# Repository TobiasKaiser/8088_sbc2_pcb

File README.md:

8088_scb2
========

See [my website][1] for more information on this PCB.

Firmware
--------

The corresponding firmware can be found in the [8088_sbc2_firmware][2] repository.

License
-------

* FT232RL component comes from a [component collection][3] from Werner Almesberger: 

Everything else:

Copyright (c) 2016 Tobias Kaiser <mail@tb-kaiser.de>

Permission is hereby granted, free of charge, to any person obtaining a copy of this hardware, software, and associated documentation files (the "Product"), to deal in the Product without restriction, including without limitation the rights to use, copy, modify, merge, publish, distribute, sublicense, and/or sell copies of the Product, and to permit persons to whom the Product is furnished to do so, subject to the following conditions:

The above copyright notice and this permission notice shall be included in all copies or substantial portions of the Product.

THE PRODUCT IS PROVIDED "AS IS", WITHOUT WARRANTY OF ANY KIND, EXPRESS OR IMPLIED, INCLUDING BUT NOT LIMITED TO THE WARRANTIES OF MERCHANTABILITY, FITNESS FOR A PARTICULAR PURPOSE AND NONINFRINGEMENT. IN NO EVENT SHALL THE AUTHORS OR COPYRIGHT HOLDERS BE LIABLE FOR ANY CLAIM, DAMAGES OR OTHER LIABILITY, WHETHER IN AN ACTION OF CONTRACT, TORT OR OTHERWISE, ARISING FROM, OUT OF OR IN CONNECTION WITH THE PRODUCT OR THE USE OR OTHER DEALINGS IN THE PRODUCT.

[1]: http://www.tb-kaiser.de/pcbs/8088_sbc2_2016_12_22/
[2]: https://github.com/TobiasKaiser/8088_sbc2_firmware/
[3]: http://projects.qi-hardware.com/index.php/p/kicad-libs/source/tree/master/components/ft232rl.lib

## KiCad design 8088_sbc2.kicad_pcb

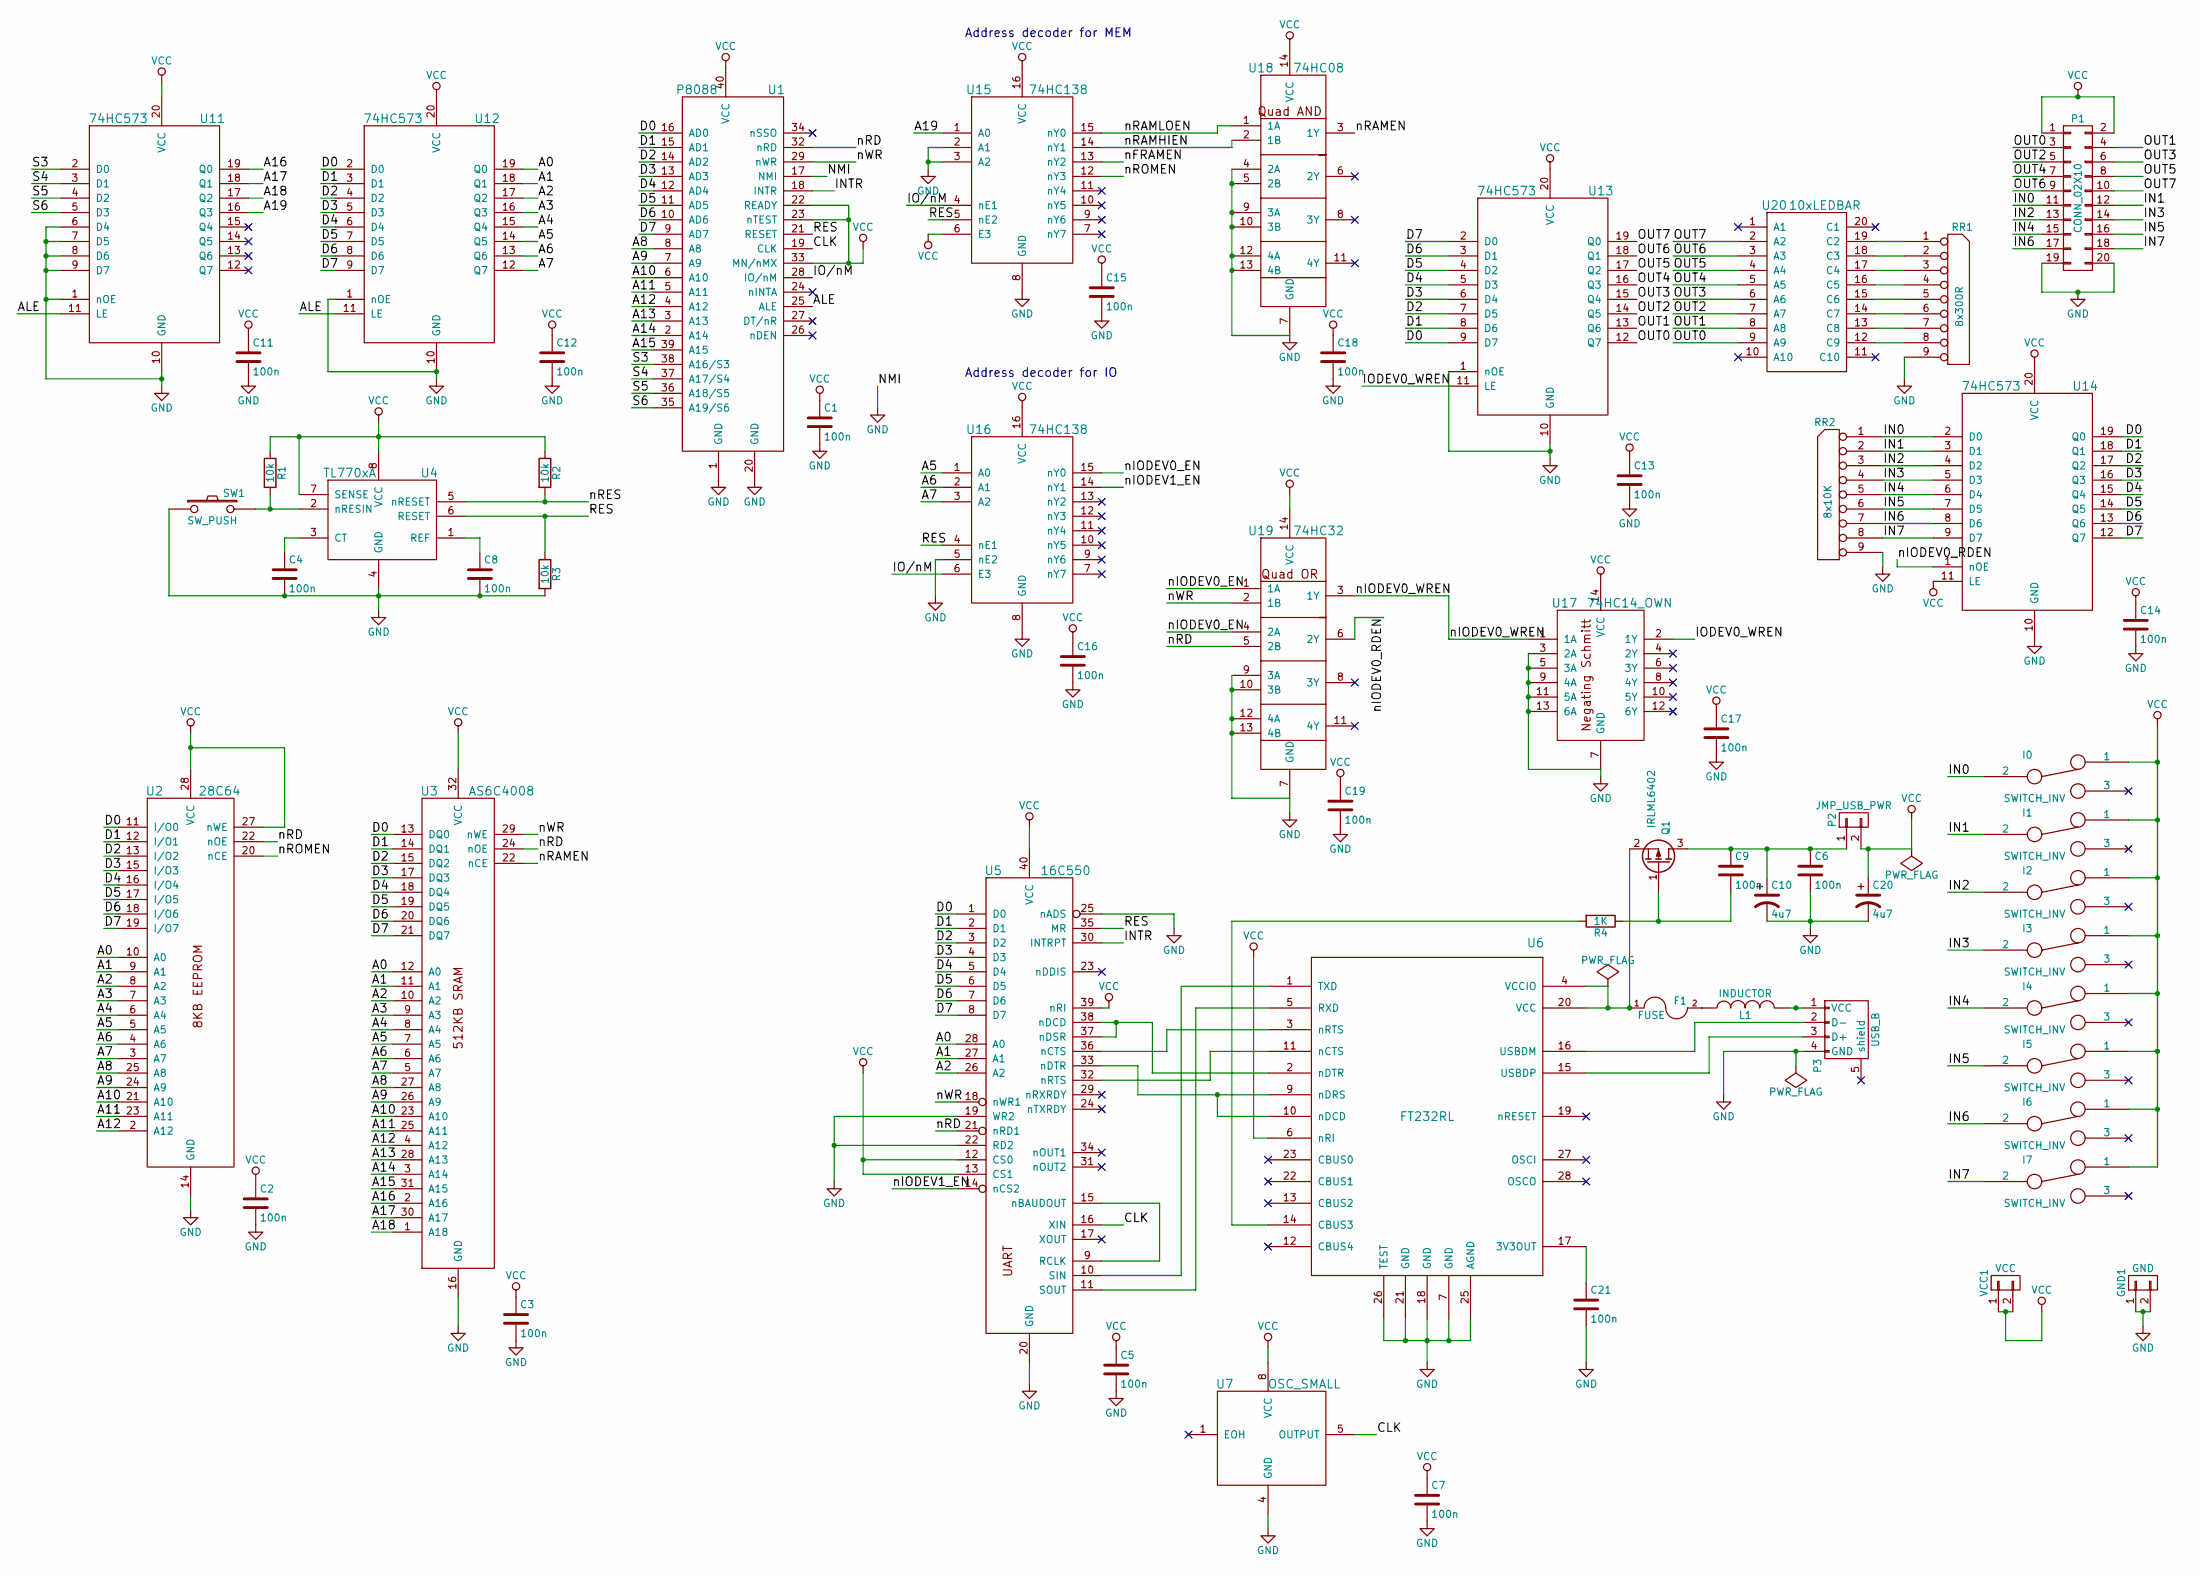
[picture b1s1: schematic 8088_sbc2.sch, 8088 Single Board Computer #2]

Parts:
C1, C2, C3, C4, C5, C6, C7, C8, C9, C11, C12, C13, C14, C15, C16, C17, C18, C19, C21: 100n; C_Disc_D3_P2.5
C10: 4u7; C_Radial_D6.3_L11.2_P2.5
C20: 4u7; C_Radial_D7.5_L11.2_P2.5
F1: FUSE; C_1206_HandSoldering
GND1: GND; Pin_Header_Straight_1x02
I0, I1, I2, I3, I4, I5, I6, I7: SWITCH_INV; EG1218
L1: INDUCTOR; C_0805_HandSoldering
P1: CONN_02X10; Pin_Header_Straight_2x10
P2: JMP_USB_PWR; Pin_Header_Straight_1x02
P3: USB_B
Q1: IRLML6402; SOT-23_Handsoldering
R1, R2, R3: 10k; Resistor_Horizontal_RM7mm
R4: 1K; R_0805_HandSoldering
RR1: 8x300R; Pin_Header_Straight_1x09
RR2: 8x10K; Pin_Header_Straight_1x09
SW1: SW_PUSH; SW_PUSH_6mm
U1: P8088; DIP-40_W15.24mm
U2: 28C64; DIP-28_W15.24mm
U3: AS6C4008; DIP-32_W15.24mm
U4: TL770xA; DIP-8_W7.62mm
U5: 16C550; DIP-40_W15.24mm
U6: FT232RL; SSOP-28_5.3x10.2mm_Pitch0.65mm
U7: OSC_SMALL; DIP-8_W7.62mm
U11, U12, U13, U14: 74HC573; DIP-20_W7.62mm
U15, U16: 74HC138; DIP-16_W7.62mm
U17: 74HC14_OWN; DIP-14_W7.62mm
U18: 74HC08; DIP-14_W7.62mm
U19: 74HC32; DIP-14_W7.62mm
U20: 10xLEDBAR; DIP-20_W7.62mm
VCC1: VCC; Pin_Header_Straight_1x02

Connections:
/A0: U2.10 (A0), U3.12 (A0), U5.28 (A0), U12.19 (Q0)
/A1: U2.9 (A1), U3.11 (A1), U5.27 (A1), U12.18 (Q1)
/A2: U2.8 (A2), U3.10 (A2), U5.26 (A2), U12.17 (Q2)
/A3: U2.7 (A3), U3.9 (A3), U12.16 (Q3)
/A4: U2.6 (A4), U3.8 (A4), U12.15 (Q4)
/A5: U2.5 (A5), U3.7 (A5), U12.14 (Q5), U16.1 (A0)
/A6: U2.4 (A6), U3.6 (A6), U12.13 (Q6), U16.2 (A1)
/A7: U2.3 (A7), U3.5 (A7), U12.12 (Q7), U16.3 (A2)
/A8: U1.8 (A8), U2.25 (A8), U3.27 (A8)
/A9: U1.7 (A9), U2.24 (A9), U3.26 (A9)
/A10: U1.6 (A10), U2.21 (A10), U3.23 (A10)
/A11: U1.5 (A11), U2.23 (A11), U3.25 (A11)
/A12: U1.4 (A12), U2.2 (A12), U3.4 (A12)
/A13: U1.3 (A13), U3.28 (A13)
/A14: U1.2 (A14), U3.3 (A14)
/A15: U1.39 (A15), U3.31 (A15)
/A16: U3.2 (A16), U11.19 (Q0)
/A17: U3.30 (A17), U11.18 (Q1)
/A18: U3.1 (A18), U11.17 (Q2)
/A19: U11.16 (Q3), U15.1 (A0)
/ALE: U1.25 (ALE), U11.11 (LE), U12.11 (LE)
/CLK: U1.19 (CLK), U5.16 (XIN), U7.5 (OUTPUT)
/D0: U1.16 (AD0), U2.11 (I/O0), U3.13 (DQ0), U5.1 (D0), U12.2 (D0), U13.9 (D7), U14.19 (Q0)
/D1: U1.15 (AD1), U2.12 (I/O1), U3.14 (DQ1), U5.2 (D1), U12.3 (D1), U13.8 (D6), U14.18 (Q1)
/D2: U1.14 (AD2), U2.13 (I/O2), U3.15 (DQ2), U5.3 (D2), U12.4 (D2), U13.7 (D5), U14.17 (Q2)
/D3: U1.13 (AD3), U2.15 (I/O3), U3.17 (DQ3), U5.4 (D3), U12.5 (D3), U13.6 (D4), U14.16 (Q3)
/D4: U1.12 (AD4), U2.16 (I/O4), U3.18 (DQ4), U5.5 (D4), U12.6 (D4), U13.5 (D3), U14.15 (Q4)
/D5: U1.11 (AD5), U2.17 (I/O5), U3.19 (DQ5), U5.6 (D5), U12.7 (D5), U13.4 (D2), U14.14 (Q5)
/D6: U1.10 (AD6), U2.18 (I/O6), U3.20 (DQ6), U5.7 (D6), U12.8 (D6), U13.3 (D1), U14.13 (Q6)
/D7: U1.9 (AD7), U2.19 (I/O7), U3.21 (DQ7), U5.8 (D7), U12.9 (D7), U13.2 (D0), U14.12 (Q7)
/IN0: I0.2, P1.11, RR2.1 (COM), U14.2 (D0)
/IN1: I1.2, P1.12, RR2.2, U14.3 (D1)
/IN2: I2.2, P1.13, RR2.3, U14.4 (D2)
/IN3: I3.2, P1.14, RR2.4, U14.5 (D3)
/IN4: I4.2, P1.15, RR2.5, U14.6 (D4)
/IN5: I5.2, P1.16, RR2.6, U14.7 (D5)
/IN6: I6.2, P1.17, RR2.7, U14.8 (D6)
/IN7: I7.2, P1.18, RR2.8, U14.9 (D7)
/INTR: U1.18 (INTR), U5.30 (INTRPT)
/IO/nM: U1.28 (IO/nM), U15.4 (nE1), U16.6 (E3)
/IODEV0_WREN: U13.11 (LE), U17.2 (1Y)
/OUT0: P1.3, U13.12 (Q7), U20.9 (A9)
/OUT1: P1.4, U13.13 (Q6), U20.8 (A8)
/OUT2: P1.5, U13.14 (Q5), U20.7 (A7)
/OUT3: P1.6, U13.15 (Q4), U20.6 (A6)
/OUT4: P1.7, U13.16 (Q3), U20.5 (A5)
/OUT5: P1.8, U13.17 (Q2), U20.4 (A4)
/OUT6: P1.9, U13.18 (Q1), U20.3 (A3)
/OUT7: P1.10, U13.19 (Q0), U20.2 (A2)
/RES: R3.1, U1.21 (RESET), U4.6 (RESET), U5.35 (MR), U15.5 (nE2), U16.4 (nE1)
/S3: U1.38 (A16/S3), U11.2 (D0)
/S4: U1.37 (A17/S4), U11.3 (D1)
/S5: U1.36 (A18/S5), U11.4 (D2)
/S6: U1.35 (A19/S6), U11.5 (D3)
/nFRAMEN: U15.13 (nY2)
/nIODEV0_EN: U16.15 (nY0), U19.1 (1A), U19.4 (2A)
/nIODEV0_RDEN: U14.1 (nOE), U19.6 (2Y)
/nIODEV0_WREN: U17.1 (1A), U19.3 (1Y)
/nIODEV1_EN: U5.14 (nCS2), U16.14 (nY1)
/nRAMEN: U3.22 (nCE), U18.3 (1Y)
/nRAMHIEN: U15.14 (nY1), U18.2 (1B)
/nRAMLOEN: U15.15 (nY0), U18.1 (1A)
/nRD: U1.32 (nRD), U2.22 (nOE), U3.24 (nOE), U5.21 (nRD1), U19.5 (2B)
/nRES: R2.2, U4.5 (nRESET)
/nROMEN: U2.20 (nCE), U15.12 (nY3)
/nWR: U1.29 (nWR), U3.29 (nWE), U5.18 (nWR1), U19.2 (1B)
GND: C1.2, C2.2, C3.2, C4.2, C5.2, C6.2, C7.2, C8.2, C10.2, C11.2, C12.2, C13.2, C14.2, C15.2, C16.2, C17.2, C18.2, C19.2, C20.2, C21.2, GND1.1, GND1.2, P1.19, P1.20, P3.4 (GND), R3.2, RR1.9, RR2.9, SW1.1, U1.1 (GND), U1.17 (NMI), U1.20 (GND), U2.14 (GND), U3.16 (GND), U4.4 (GND), U5.19 (WR2), U5.20 (GND), U5.22 (RD2), U5.25 (nADS), U6.7 (GND), U6.18 (GND), U6.21 (GND), U6.25 (AGND), U6.26 (TEST), U7.4 (GND), U11.1 (nOE), U11.6 (D4), U11.7 (D5), U11.8 (D6), U11.9 (D7), U11.10 (GND), U12.1 (nOE), U12.10 (GND), U13.1 (nOE), U13.10 (GND), U14.10 (GND), U15.2 (A1), U15.3 (A2), U15.8 (GND), U16.5 (nE2), U16.8 (GND), U17.3 (2A), U17.5 (3A), U17.7 (GND), U17.9 (4A), U17.11 (5A), U17.13 (6A), U18.4 (2A), U18.5 (2B), U18.7 (GND), U18.9 (3A), U18.10 (3B), U18.12 (4A), U18.13 (4B), U19.7 (GND), U19.9 (3A), U19.10 (3B), U19.12 (4A), U19.13 (4B)
unnamed: C4.1, U4.3 (CT)
unnamed: C8.1, U4.1 (REF)
unnamed: C9.2, Q1.1 (G), R4.1
unnamed: C6.1, C9.1, C10.1, P2.1, Q1.3 (D)
unnamed: C21.1, U6.17 (3V3OUT)
unnamed: F1.1, Q1.2 (S), U6.4 (VCCIO), U6.20 (VCC)
unnamed: F1.2, L1.1
unnamed: L1.2, P3.1 (VCC)
unnamed: P3.2 (D-), U6.16 (USBDM)
unnamed: P3.3 (D+), U6.15 (USBDP)
unnamed: R1.2, SW1.2, U4.2 (nRESIN)
unnamed: R4.2, U6.14 (CBUS3)
unnamed: RR1.1 (COM), U20.19 (C2)
unnamed: RR1.2, U20.18 (C3)
unnamed: RR1.3, U20.17 (C4)
unnamed: RR1.4, U20.16 (C5)
unnamed: RR1.5, U20.15 (C6)
unnamed: RR1.6, U20.14 (C7)
unnamed: RR1.7, U20.13 (C8)
unnamed: RR1.8, U20.12 (C9)
unnamed: U5.10 (SIN), U6.1 (TXD)
unnamed: U5.11 (SOUT), U6.5 (RXD)
unnamed: U5.9 (RCLK), U5.15 (nBAUDOUT)
unnamed: U5.32 (nRTS), U6.11 (nCTS)
unnamed: U5.33 (nDTR), U6.9 (nDRS), U6.10 (nDCD)
unnamed: U5.36 (nCTS), U6.3 (nRTS)
unnamed: U5.37 (nDSR), U5.38 (nDCD), U6.2 (nDTR)
VCC: C1.1, C2.1, C3.1, C5.1, C7.1, C11.1, C12.1, C13.1, C14.1, C15.1, C16.1, C17.1, C18.1, C19.1, C20.1, I0.1, I1.1, I2.1, I3.1, I4.1, I5.1, I6.1, I7.1, P1.1, P1.2, P2.2, R1.1, R2.1, U1.22 (READY), U1.23 (nTEST), U1.33 (MN/nMX), U1.40 (VCC), U2.27 (nWE), U2.28 (VCC), U3.32 (VCC), U4.7 (SENSE), U4.8 (VCC), U5.12 (CS0), U5.13 (CS1), U5.39 (nRI), U5.40 (VCC), U6.6 (nRI), U7.8 (VCC), U11.20 (VCC), U12.20 (VCC), U13.20 (VCC), U14.11 (LE), U14.20 (VCC), U15.6 (E3), U15.16 (VCC), U16.16 (VCC), U17.14 (VCC), U18.14 (VCC), U19.14 (VCC), VCC1.1, VCC1.2

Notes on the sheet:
Address decoder for MEM
Address decoder for IO

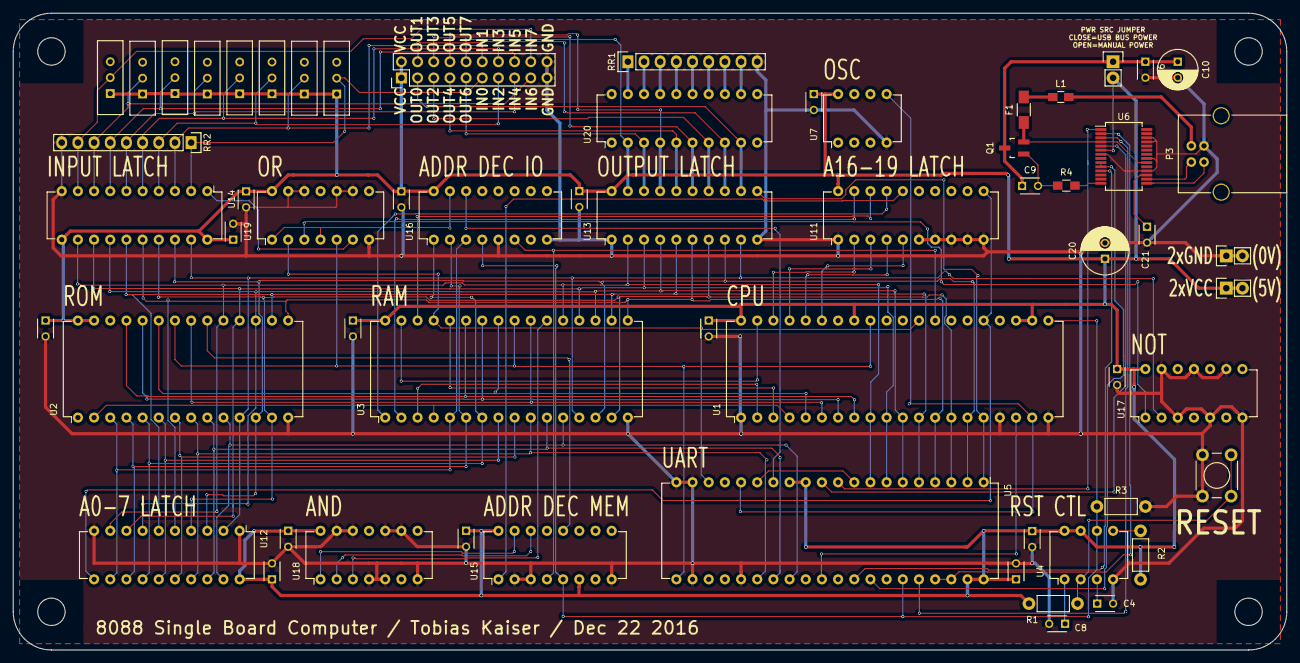
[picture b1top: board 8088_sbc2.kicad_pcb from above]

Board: 2 copper layers, 200.0 x 100.0 mm, 61 parts (0 on the bottom side), 94 nets.

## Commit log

2016-10-11 added all(?) important parts to lib
2016-10-12 working on schematic
2016-10-21 am schaltplan weitergearbeitet
2016-10-28 schematic erc good.
2016-12-21 looks good :D
2016-12-22 version with new design rules
2016-12-22 test
2016-12-22 shitty kicad fucked it up while saving. fuck it.
2016-12-22 zwischenstand
2016-12-22 zwischenstand2
2016-12-22 zwischenstand3
2016-12-22 zwischenstand5
2016-12-22 DRC w/ cheaper tolerances successful
2016-12-22 weiter
2016-12-22 almost ready for submission
2016-12-22 DRC and ERC OK. making some gerbers now?!
2016-12-22 Gerber erzeugt, sieht gut aus, wird bald bestellt.
2016-12-22 added all files that were not added yet :D
2017-03-18 removed datasheets from repo
2017-03-18 added minimal documentation
